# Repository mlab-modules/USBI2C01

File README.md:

# USBI2C01A - USB to I²C master converter

USBI2C01A is USB to I²C master adapter, it provides you ability to connect almost any I2C/SMBUS sensor or other device to a computer trought USB.
Converter is based on [CP2112](https://www.silabs.com/interface/usb-bridges/classic/device.cp2112?tab=specs) integrated USB brigde with native Linux kernel support. 
Therefore device create kernel accesible I2C interface intstantly on almost any Linux distributions.
If your computer doesn't support CP2112 converter, it's possible to use the USB-HID interface of the converter.
Thanks to that, the device can be used with other operating systems as well, as Windows or Android.

The module is connected to computer using a USB-B connector, which provides a quality connection to the computer. The module contains three LED diodes that indicate power and communication via the I2C bus in the default configuration. The communication pins are doubled, so you will have enough space to connect your circuit.

I2C is connected to the 5-pin header in the MLAB I2C pinout. This is specific in that the rotation of cable (connector) will only result in not functioning state. However, there is no risk of electrical damage. Using jumpers, it is possible to set the power supply voltage in the I2C bus connector. This can either be 5V from USB, which is protected by a 750 mA fuse, or 3.45V from the integrated LDO with a maximum allowed load of 100 mA.

The converter is equipped with a set of GPIO ports that can be controlled via USB. In addition to communication via I2C, you can, for example, check the status of digital signals or control them with software. Similarly, you can use LEDs on the module to indicate your own states because they are software-controllable. 

### Parameters
 * USB-HID to SMBus (I2C) master bridge
 * 8 GPIO ports (2 equipted with LED indicators)
   * Configurable as Input/Output, Open-drain/Push-pull
   * Configurable as clock output (48 MHz to 94 kHz)
 * Selectable 5V or 3.3V power supply
 * USB-B - FullSpeed USB support (up to 12 Mbps)
   * Powered from USB
 * Support in linux kernel
 * Configurable clock speed, 7bit i2c adressing
 * Ready to use 

## How to get this device? 

This device is sold by [Universal Scientific Technologies s.r.o.](www.ust.cz). You can buy it online trought [Tindie MLAB store](https://www.tindie.com/products/33745/) or interested in more our products, do not be afraid to [contact us](mailto:sale@ust.cz
).

## Drivers and software
The USB device behaves as a standard [USB-HID](https://en.wikipedia.org/wiki/USB_human_interface_device_class) device, so you do not need non-standard drivers. It also allows control of devices in the I2C system bus.

In case of Linux the drivers are available in kernel. Therefore the module creates the system-wide I2C bus. This is the same interface that you can known from thesingle-board computers like Raspberry Pi. Thanks to this, you will be able to run your Raspberry Pi programs directly on your computer.

## Usage
The functional examples are available in [pymblab](https://github.com/MLAB-project/pymlab) control library. The details are available on [MLAB wiki](https://wiki.mlab.cz/doku.php?id=en:usbi2c). The Pymlab library supports accessing the device both through the I2C interface in the Linux kernel and through the USB-HID interface. Thanks to this, you can use these modules on different operating systems.

## Hardware

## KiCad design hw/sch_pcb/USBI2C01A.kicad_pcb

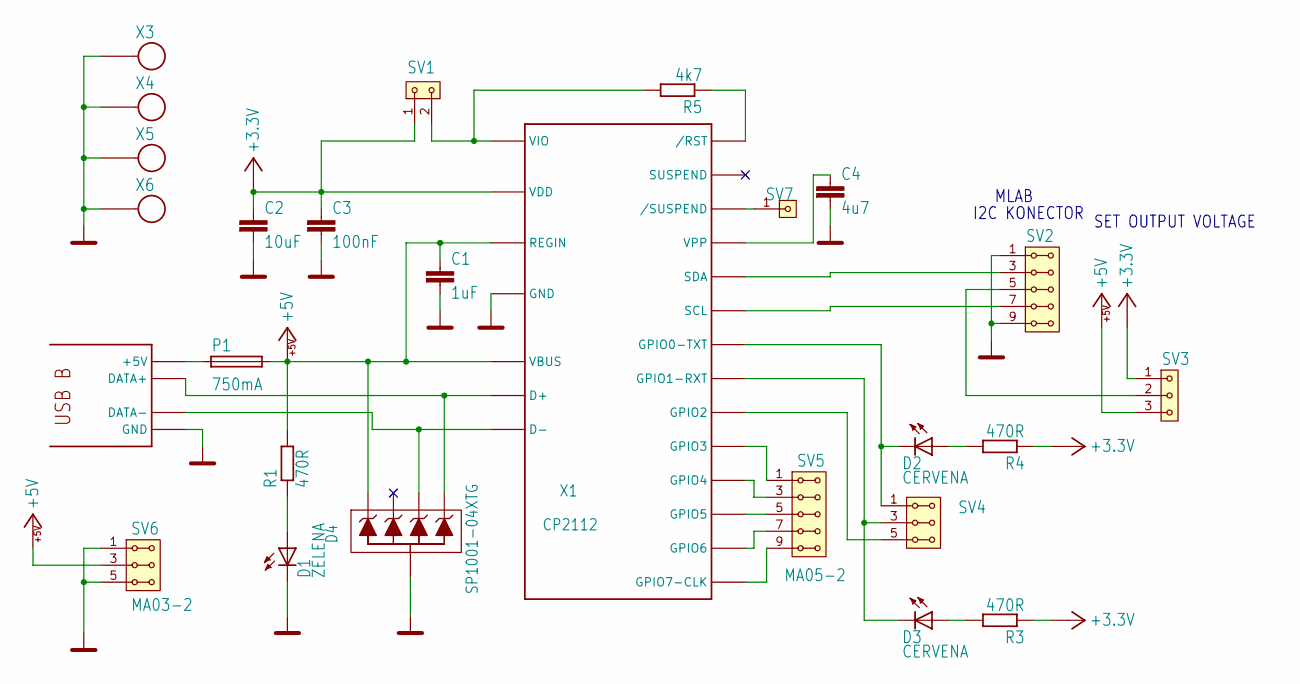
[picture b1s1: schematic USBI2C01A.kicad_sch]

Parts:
C1: 1uF; C_0805_2012Metric
C2: 10uF; C_0805_2012Metric
C3: 100nF; C_0805_2012Metric
C4: 4u7; C_0805_2012Metric
D1: ZELENA; 1206_2
D2, D3: CERVENA; 1206_2
D4: SP1001-04XTG; SOT553
P1: 750mA; 1812
R1, R3, R4: 470R; 0805
R5: 4k7; 0805
SV1: MA02-1
SV2, SV5: MA05-2
SV3: MA03-1
SV4, SV6: MA03-2
SV7: MA01-1
X1: CP2112; QFN-24
X2: USB_B
X3, X4, X5, X6: SROUB3M

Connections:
+3.3V: C2.1, C3.1, R3.1, R4.1, SV1.1, SV3.1, X1.P$6 (VDD)
+5V: C1.1, D4.1, P1.2, R1.2, SV3.3, SV6.3, SV6.4, X1.P$7 (REGIN), X1.P$8 (VBUS)
GND: C1.2, C2.2, C3.2, C4.2, D1.K (C), D4.2, SV2.1, SV2.2, SV2.9, SV2.10, SV6.1, SV6.2, SV6.5, SV6.6, X1.P$2 (GND), X1.P$25 (GND), X2.4 (GND), X2.GND, X2.GND2 (GND), X3.P$1, X4.P$1, X5.P$1, X6.P$1
unnamed: C4.1, X1.P$16 (VPP)
unnamed: D1.A, R1.1
unnamed: D2.A, R4.2
unnamed: D2.K (C), SV4.1, SV4.2, X1.P$23 (GPIO0-TXT)
unnamed: D3.A, R3.2
unnamed: D4.4, X1.P$4 (D-), X2.2 (DATA-)
unnamed: D4.5, X1.P$3 (D+), X2.3 (DATA+)
unnamed: P1.1, X2.1 (+5V)
unnamed: R5.1, X1.P$9 (/RST)
unnamed: R5.2, SV1.2, X1.P$5 (VIO)
unnamed: SV2.5, SV2.6, SV3.2
unnamed: SV5.1, SV5.2, X1.P$20 (GPIO3)
unnamed: SV7.1, X1.P$17 (/SUSPEND)
unnamed: SV2.3, SV2.4, X1.P$1 (SDA)
unnamed: SV5.9, SV5.10, X1.P$12 (GPIO7-CLK)
unnamed: SV5.7, SV5.8, X1.P$13 (GPIO6)
unnamed: SV5.5, SV5.6, X1.P$14 (GPIO5)
unnamed: SV5.3, SV5.4, X1.P$15 (GPIO4)
unnamed: SV4.5, SV4.6, X1.P$21 (GPIO2)
unnamed: D3.K (C), SV4.3, SV4.4, X1.P$22 (GPIO1-RXT)
unnamed: SV2.7, SV2.8, X1.P$24 (SCL)

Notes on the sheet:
MLAB
I2C KONECTOR
SET OUTPUT VOLTAGE

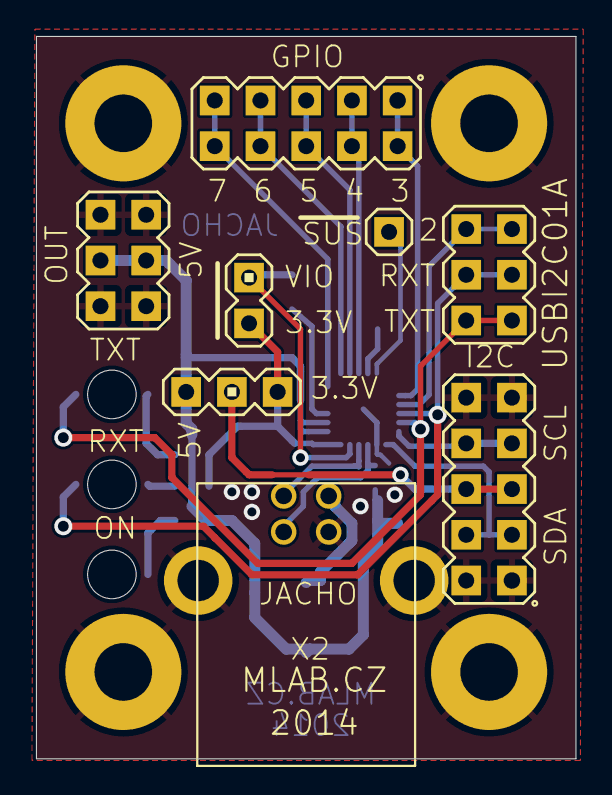
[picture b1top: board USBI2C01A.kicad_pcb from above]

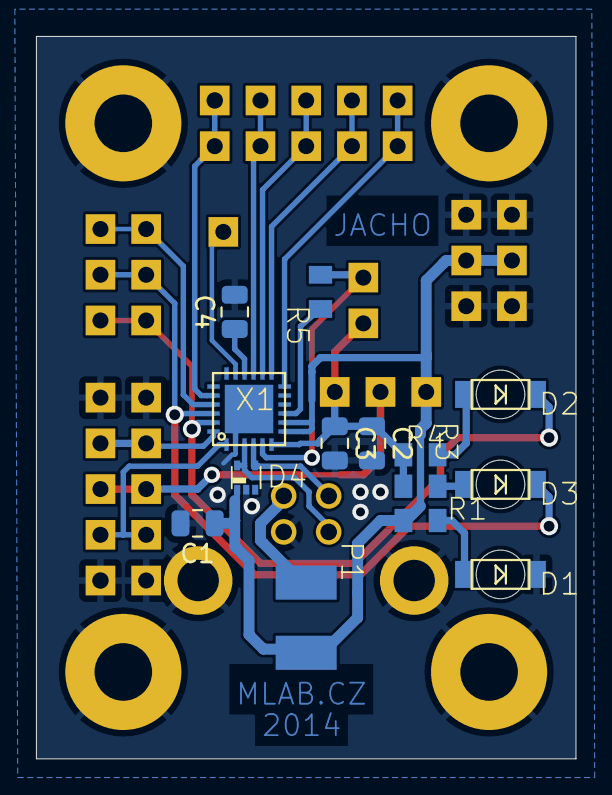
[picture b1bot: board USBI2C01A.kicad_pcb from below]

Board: 2 copper layers, 30.0 x 40.1 mm, 26 parts (14 on the bottom side), 24 nets.

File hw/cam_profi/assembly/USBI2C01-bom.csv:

Component,Description,Part,References,Value,Footprint,Quantity Per PCB,Datasheet,ust_id
1,,C0805,C3,100nF,C_0805_2012Metric,1,,5c70984712875079b91f8b4c
2,,C0805,C1,1uF,C_0805_2012Metric,1,,5c70984712875079b91f8b50
3,,C0805,C4,4u7,C_0805_2012Metric,1,,5e3ff8fc1287502a33bad7a3
4,,C0805,C2,10uF,C_0805_2012Metric,1,,5c70984812875079b91f8bbd
5,,LED1206_2,D1,Green,1206_2,1,,5c70984412875079b91f8895
6,,LED1206_2,D2D3,Red,1206_2,2,,5c70984412875079b91f8896
7,,D_4xZENER,D4,SP1001-04XTG,SOT553,1,,5c70984512875079b91f88cc
8,,POJISTKA_1812,P1,750mA,1812,1,,5c70984512875079b91f88d2
9,,R0805,R1R3R4,470R,0805,3,,5c70984512875079b91f8986
10,,R0805,R5,4k7,0805,1,,5c70984612875079b91f8995
11,1x01 2.54 mm pitch header,HEADER_1x01,SV7,MA01-1,MA01-1,1,,
12,1x02 2.54 mm pitch header,HEADER_1x02,SV1,MA02-1,MA02-1,1,,
13,1x03 2.54 mm pitch header,HEADER_1x03,SV3,MA03-1,MA03-1,1,,
14,"2x03 2.54 mm pitch header, 2 pins next to each other are connected",HEADER_2x03_PARALLEL,SV4SV6,MA03-2,MA03-2,2,,
15,"2x05 2.54 mm pitch header, 2 pins next to each other are connected",HEADER_2x05_PARALLEL,SV2SV5,MA05-2,MA05-2,2,,
16,,CP2112,X1,CP2112,QFN-24,1,,5c70984612875079b91f89b2
17,,SROUB3M,X3X4X5X6,SROUB3M,SROUB3M,4,,
18,,USB_B,X2,USB_B,USB_B,1,,5c70984412875079b91f87a8

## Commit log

2017-08-22 rename category folders
2017-08-22 rename files and module folders
2017-08-22 change images path
2017-08-22 create hw folder
2017-08-22 change filepaths
2017-08-22 rm empty json html files, rename module.json files
2017-08-22 new .json files
2017-09-01 Edit - Parts List
2017-11-02 [MLABweb] 2017-11-02 00:09:26 USBI2C01A
2018-02-27 [MLABweb] 2018-02-27 23:33:45 USBI2C01A
2018-11-05 Presun obrazku do slozky img. Pregenerovani dokumentaci.
2020-11-11 update datasheets.
2022-04-05 Transfer of the Eagle project to KiCad
2022-04-05 Renaming the Kicad project
2022-04-05 Edit schema a vlozeni UST_ID
2022-04-05 pridani actions
2022-04-05 uprava cesty
2022-04-05 Update actions products
2022-04-05 Uprava projektovych dat
2022-04-05 uprava generovani dat
2022-04-05 update submodule
2022-04-05 aktualizace assets
2022-04-05 Removing old czech version of the readme.
2022-04-05 Add license
2022-04-06 automated commit; add github actions
2023-02-13 Translate and cleanup schematics.
2023-02-13 Update GitHub actions.
2023-02-13 Update metadata files
2023-02-13 Renaming the KiCAD project to name without revision.
2023-02-13 Update submodule.
2023-02-13 Update workflow files
2023-02-15 Use kicad_pcb as BOM in kitspace.yaml
2023-05-25 update assets
2023-05-25 update submodules
2023-07-05 automated commit; rename source files to new naming convence
2024-07-08 Update metadata.yaml
    Fix tindie link and title photo.
2024-12-07 Update README.md
    Fix link to tindie store.
